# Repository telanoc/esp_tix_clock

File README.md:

=========================================================================

Module: esp tix clock

Date: 13 November 2015

Author: Pete Cervasio <cervasio@airmail.net>

=========================================================================

This project is a TIX clock running on an ESP-01 module.  Since the I/O
is limited, the two available pins are used for an i2c bus to drive a
port expander.  That handles the 27 LEDs as a 9x3 matrix using a ULN2803
and another transistor for the columns and three transistors to drive
the rows.  The other 4 pins read mostly-useless alarm setting buttons.
If only there was another output to use to drive some kind of alarmy
soundy thing.  Oops.  Perhaps I can modify the code so that it doesn't
send any serial data out, and take over the serial port pins.

So, what's a TIX clock?  Google is your friend, as are Bing and Yahoo.
And Youtube to an extent.

Features:

    ESP-01 module gets time from NTP - All you set is the access point
    & password.  You set the timezone before you compile.  Automatic
    changeover takes over from there.  Just don't move around a lot.
    :)

    Power is +5v, regulated to +3.3 for the ESP-01.  The clock in my
    living room is powered by your generic three-for-a-dollar USB
    power brick.

    Time library used to get NTP.  Modifications were made to make the
    time setting closer to msec accuracy (it's pretty close).  I got
    this from https://github.com/PaulStoffregen/Time if you want the
    original.

    WiFiManager used to auto-connect to the access point, and to set
    up the connection if necessary.  From AlexT
    (https://github.com/tzapu) but custom changes are stored in this
    repository.

    Timezone library (https://github.com/JChristensen/Timezone) used
    to handle automatic DST change.

    Display and Controller boards designed in Eagle 7.4 are included.
    The two boards are shared on Osh Park

        Display: https://www.oshpark.com/shared_projects/UMcsDmIr
     Controller: https://www.oshpark.com/shared_projects/IgKxO56E

    An alarm time can be set, but "oops, I need more pins"... there's
    no alarm output.  So it's not much of a feature after all.  As
	noted above, it should be possible to drop the serial port bits
	and take over those pins to be more gpio.

    A dumb 3d printed case will eventually be available on Tinkercad
    or Thingiverse or somewhere.  The one I have started is close but
    not quite there yet.

Caveats and whatnot:

    This was built using staging release esp8266-1.6.5-1160-gef26c5f

    Soldering SMTs by hand is a pain in the behind when you're older.

    Don't bring pin 9 of the display board to +5v without a current
    limiting resistor or you'll take out the 2n3904.  Don't ask how I
    know that...  the resistor on the control board should have been
    moved.
    
    ... ahh hindsight.

    male Power pins are long out the bottom of the control board to
    allow attaching a header for +5v.  That's how I did it.  If you
    have a better idea, please use it.  :)

Todo:

    Build a nice 3d printed case at the North Richland Hills Library
    Maker Spot.  I can't say enough good things about the most
    important building in NRH (and the highly important room upstairs
    that has all the fun makey bits in it).  If you live around Fort
    Worth, go visit.  It's a "soft" maker space, with no table saws or
    welder or whatnot, but that's what the Dallas maker space is good
    for.  :)

    Revamp the boards to bring out serial data, which would allow for
    setting more parameters and storing them in eeprom, like time zone
    values and stuff like that.

    Move that transistor base resistor to the display board.

Harware BOM:  This should be pretty accurate.

        1 - ESP-01
        1 - mcp23017 (so28w)
        1 - uln2803  (so18w)
        4 - MMBT3904 (sot23-bec)
        2 - BSS138 mosfets (sot-23)
        4 - standard through-hole tactile switches
        1 - AP2112K-3.3 regulator (sot-23-5)
        1 - 10uf 0805 capacitor
        2 - 0.1 uf 0805 capacitor
        1 - 1k 0805 resistor
        6 - 10k 0805 resistor
       27 - 68 ohm 0805 resistors
        3 - AA2214SURSK SMT blue LEDs
        6 - yellow SMT LEDs
        9 - red SMT LEDs
        9 - green SMT LEDs
        1 - 1x2 pin male header (extra long) 
        1 - 1x3 pin male header
        1 - 1x3 pin male header
        1 - 1x3 female header
        1 - 1x2 female header
        1 - 1x9 female header
        1 - 2x4 female header

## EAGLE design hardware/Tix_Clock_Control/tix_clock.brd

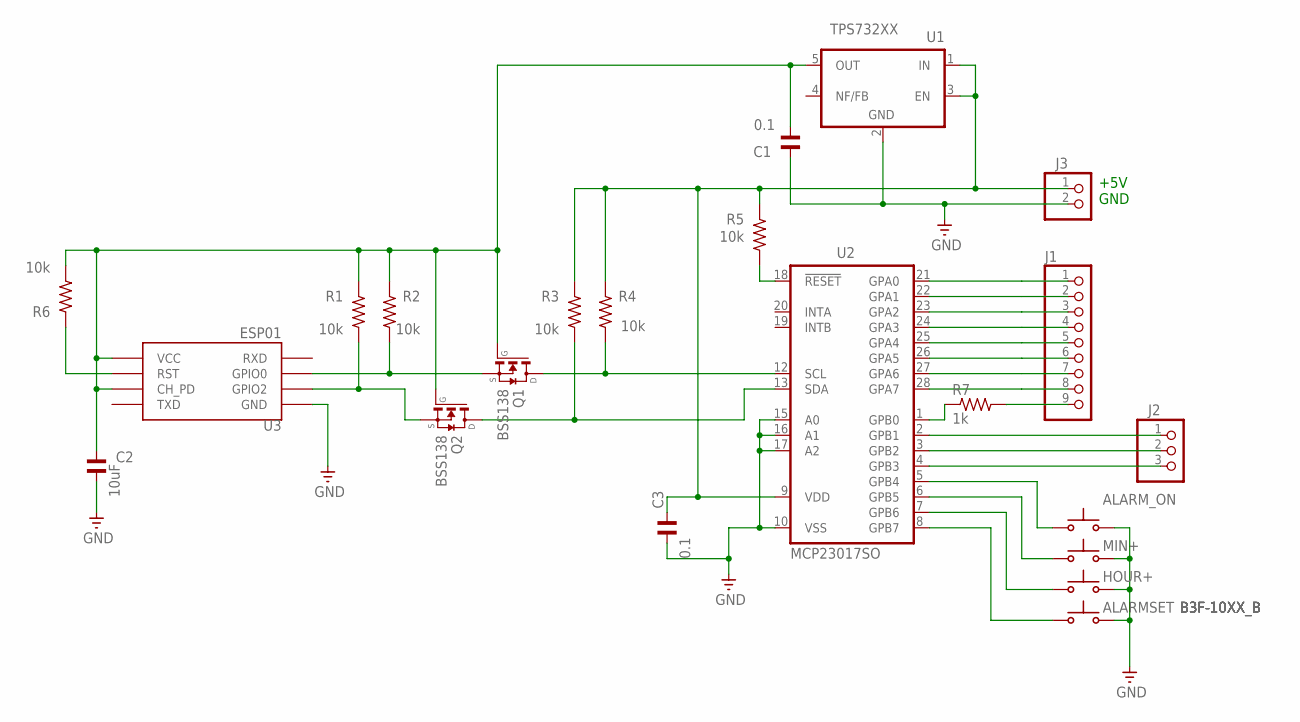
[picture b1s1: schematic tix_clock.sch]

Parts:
ALARMSET: B3F-10XX_B
ALARM_ON: B3F-10XX_B
C1, C3: 0.1; C0805
C2: 10uF; C0805
HOUR+: B3F-10XX_B
J1: PINHD-1X9; 1X09
J2: PINHD-1X3; 1X03
J3: PINHD-1X2; 1X02
MIN+: B3F-10XX_B
Q1, Q2: BSS138; SOT23
R1, R2, R3, R4, R5, R6: 10k; R0805
R7: 1k; R0805
U1: TPS732XX; SOT23-5
U2: MCP23017SO; SO28W
U3: ESP01

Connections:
GND: ALARMSET.3 (S), ALARMSET.4 (S), ALARM_ON.3 (S), ALARM_ON.4 (S), C1.2, C2.2, C3.2, HOUR+.3 (S), HOUR+.4 (S), J3.2, MIN+.3 (S), MIN+.4 (S), U1.2 (GND), U2.10 (VSS), U2.15 (A0), U2.16 (A1), U2.17 (A2), U3.GND
unnamed: J1.1, U2.21 (GPA0)
unnamed: J1.2, U2.22 (GPA1)
unnamed: J1.3, U2.23 (GPA2)
unnamed: J1.4, U2.24 (GPA3)
unnamed: J1.5, U2.25 (GPA4)
unnamed: J1.6, U2.26 (GPA5)
unnamed: J1.7, U2.27 (GPA6)
unnamed: J1.8, U2.28 (GPA7)
unnamed: J1.9, R7.2
unnamed: J2.1, U2.2 (GPB1)
unnamed: J2.2, U2.3 (GPB2)
unnamed: J2.3, U2.4 (GPB3)
unnamed: ALARM_ON.1, ALARM_ON.2, U2.5 (GPB4)
unnamed: MIN+.1, MIN+.2, U2.6 (GPB5)
unnamed: HOUR+.1, HOUR+.2, U2.7 (GPB6)
unnamed: ALARMSET.1, ALARMSET.2, U2.8 (GPB7)
unnamed: R7.1, U2.1 (GPB0)
unnamed: Q1.3 (D), R4.1, U2.12 (SCL)
unnamed: Q2.3 (D), R3.1, U2.13 (SDA)
unnamed: Q1.2 (S), R2.1, U3.GPIO0
unnamed: Q2.2 (S), R1.1, U3.GPIO2
unnamed: R5.1, U2.18 (!RESET)
unnamed: R6.1, U3.RST
VCC: C1.1, C2.1, Q1.1 (G), Q2.1 (G), R1.2, R2.2, R6.2, U1.5 (OUT), U3.CH_PD, U3.VCC
VDD: C3.1, J3.1, R3.2, R4.2, R5.2, U1.1 (IN), U1.3 (EN), U2.9 (VDD)

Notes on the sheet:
+5V GND

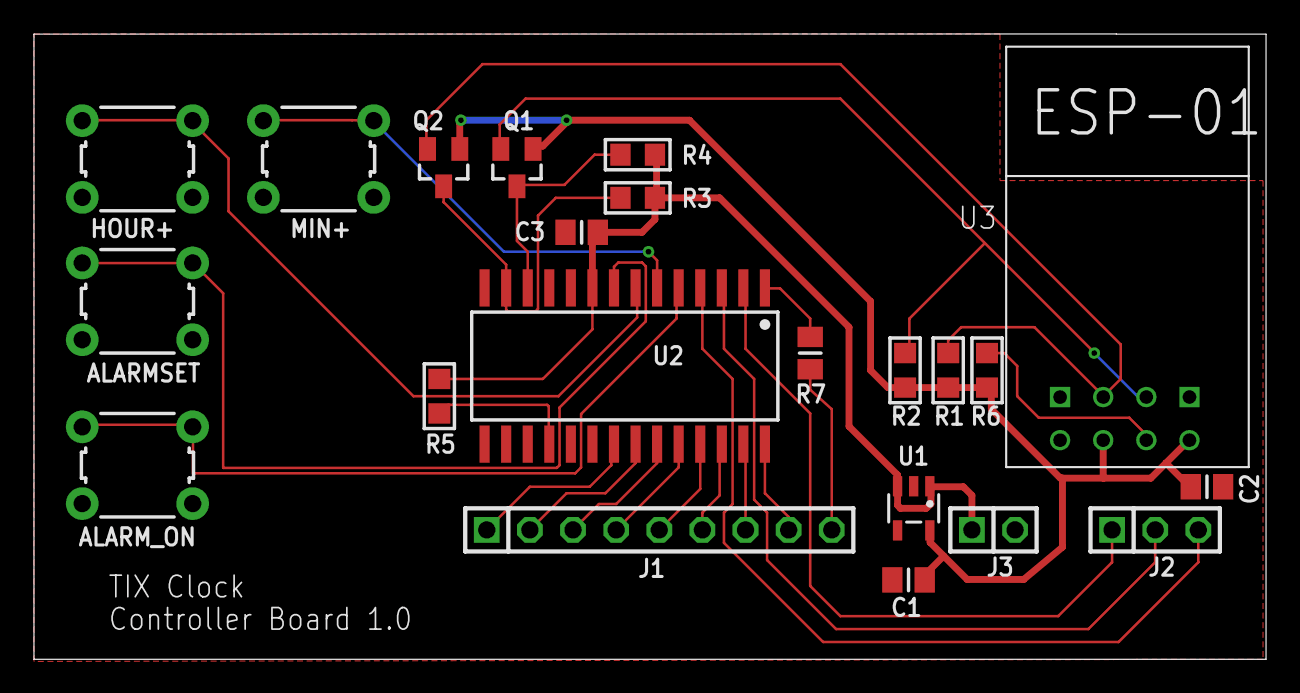
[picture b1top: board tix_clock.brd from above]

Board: 2 copper layers, 72.6 x 36.8 mm, 22 parts (0 on the bottom side), 26 nets.

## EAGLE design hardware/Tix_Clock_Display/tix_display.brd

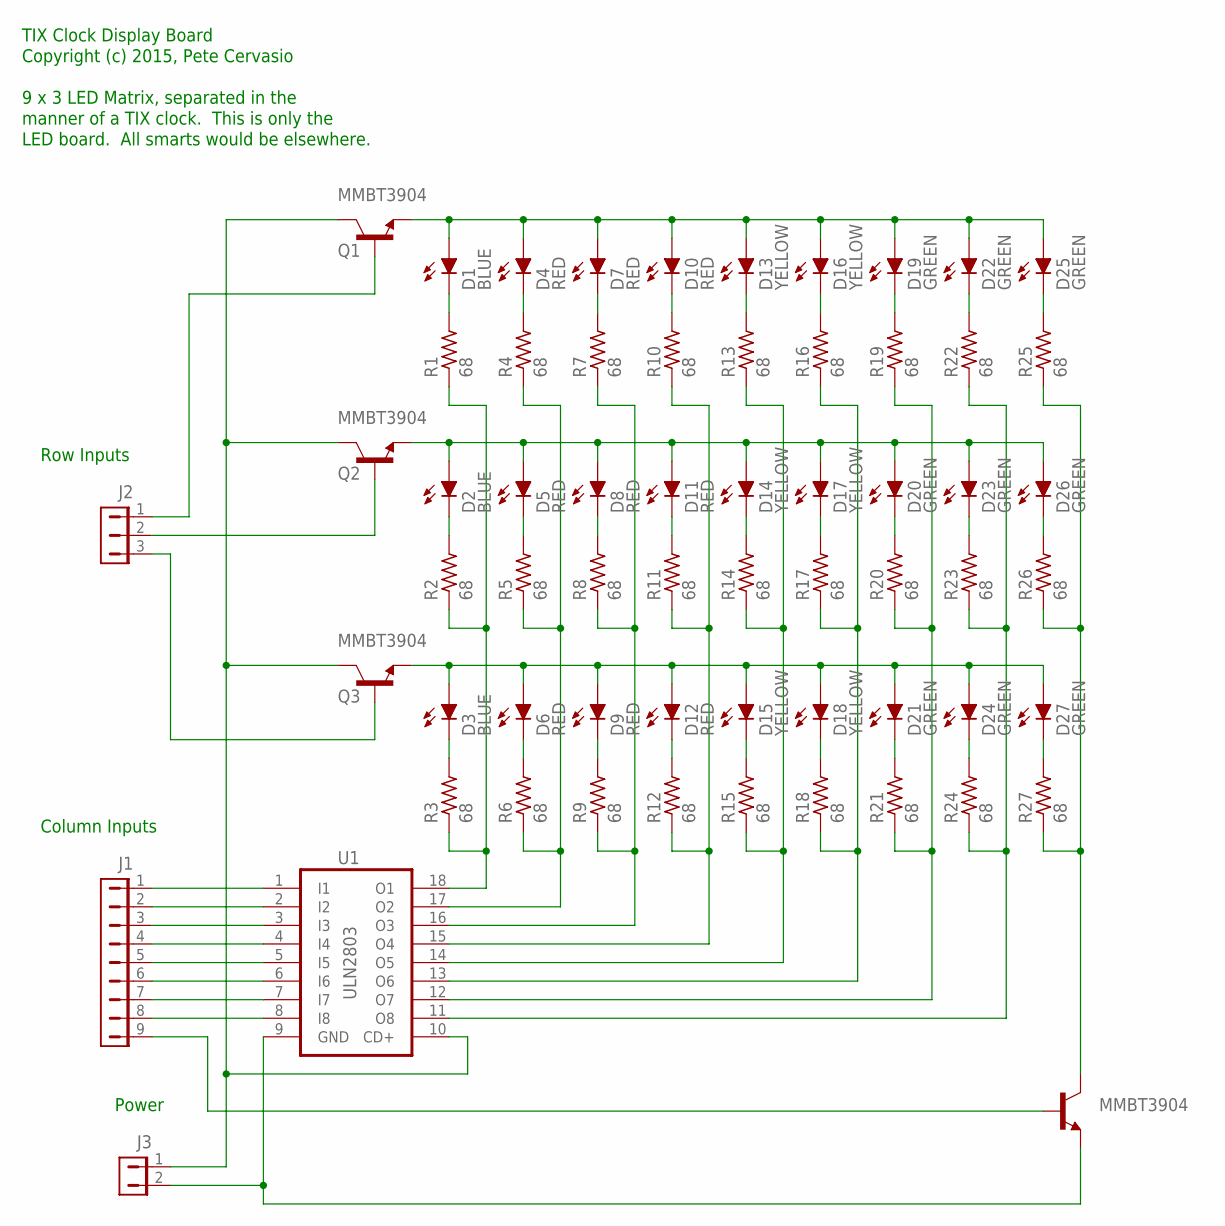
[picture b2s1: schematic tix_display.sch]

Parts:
D1, D2, D3: BLUE; AA2214SURSK
D4, D5, D6, D7, D8, D9, D10, D11, D12: RED; AA2214SURSK
D13, D14, D15, D16, D17, D18: YELLOW; AA2214SURSK
D19, D20, D21, D22, D23, D24, D25, D26, D27: GREEN; AA2214SURSK
J1: MTA09-100
J2: MTA03-100
J3: MTA02-100
Q1, Q2, Q3, Q4: MMBT3904; SOT23-BEC
R1, R2, R3, R4, R5, R6, R7, R8, R9, R10, R11, R12, R13, R14, R15, R16, R17, R18, R19, R20, R21, R22, R23, R24, R25, R26, R27: 68; M0805
U1: ULN2803; SO18W

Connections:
GND: J3.2, Q4.E, U1.9 (GND)
LEDCOL1: R1.1, R2.1, R3.1, U1.18 (O1)
LEDCOL2: R4.1, R5.1, R6.1, U1.17 (O2)
LEDCOL3: R7.1, R8.1, R9.1, U1.16 (O3)
LEDCOL4: R10.1, R11.1, R12.1, U1.15 (O4)
LEDCOL5: R13.1, R14.1, R15.1, U1.14 (O5)
LEDCOL6: R16.1, R17.1, R18.1, U1.13 (O6)
LEDCOL7: R19.1, R20.1, R21.1, U1.12 (O7)
LEDCOL8: R22.1, R23.1, R24.1, U1.11 (O8)
LEDCOL9: Q4.C, R25.1, R26.1, R27.1
unnamed: D1.A, D4.A, D7.A, D10.A, D13.A, D16.A, D19.A, D22.A, D25.A, Q1.E
unnamed: D2.A, D5.A, D8.A, D11.A, D14.A, D17.A, D20.A, D23.A, D26.A, Q2.E
unnamed: D3.A, D6.A, D9.A, D12.A, D15.A, D18.A, D21.A, D24.A, D27.A, Q3.E
unnamed: D3.C, R3.2
unnamed: D27.C, R27.2
unnamed: J2.1, Q1.B
unnamed: D24.C, R24.2
unnamed: J2.2, Q2.B
unnamed: D21.C, R21.2
unnamed: D18.C, R18.2
unnamed: D15.C, R15.2
unnamed: D12.C, R12.2
unnamed: D9.C, R9.2
unnamed: D6.C, R6.2
unnamed: D2.C, R2.2
unnamed: D5.C, R5.2
unnamed: D8.C, R8.2
unnamed: D11.C, R11.2
unnamed: D14.C, R14.2
unnamed: D17.C, R17.2
unnamed: D20.C, R20.2
unnamed: D23.C, R23.2
unnamed: D26.C, R26.2
unnamed: D1.C, R1.2
unnamed: D25.C, R25.2
unnamed: D22.C, R22.2
unnamed: D19.C, R19.2
unnamed: D16.C, R16.2
unnamed: D13.C, R13.2
unnamed: D10.C, R10.2
unnamed: D7.C, R7.2
unnamed: D4.C, R4.2
unnamed: J2.3, Q3.B
unnamed: J1.1, U1.1 (I1)
unnamed: J1.2, U1.2 (I2)
unnamed: J1.3, U1.3 (I3)
unnamed: J1.4, U1.4 (I4)
unnamed: J1.5, U1.5 (I5)
unnamed: J1.6, U1.6 (I6)
unnamed: J1.7, U1.7 (I7)
unnamed: J1.8, U1.8 (I8)
unnamed: J1.9, Q4.B
VCC: J3.1, Q1.C, Q2.C, Q3.C, U1.10 (CD+)

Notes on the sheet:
Row Inputs
Column Inputs
Power
TIX Clock Display Board Copyright (c) 2015, Pete Cervasio 9 x 3 LED Matrix, separated in the manner of a TIX clock. This is only the LED board. All smarts would be elsewhere.

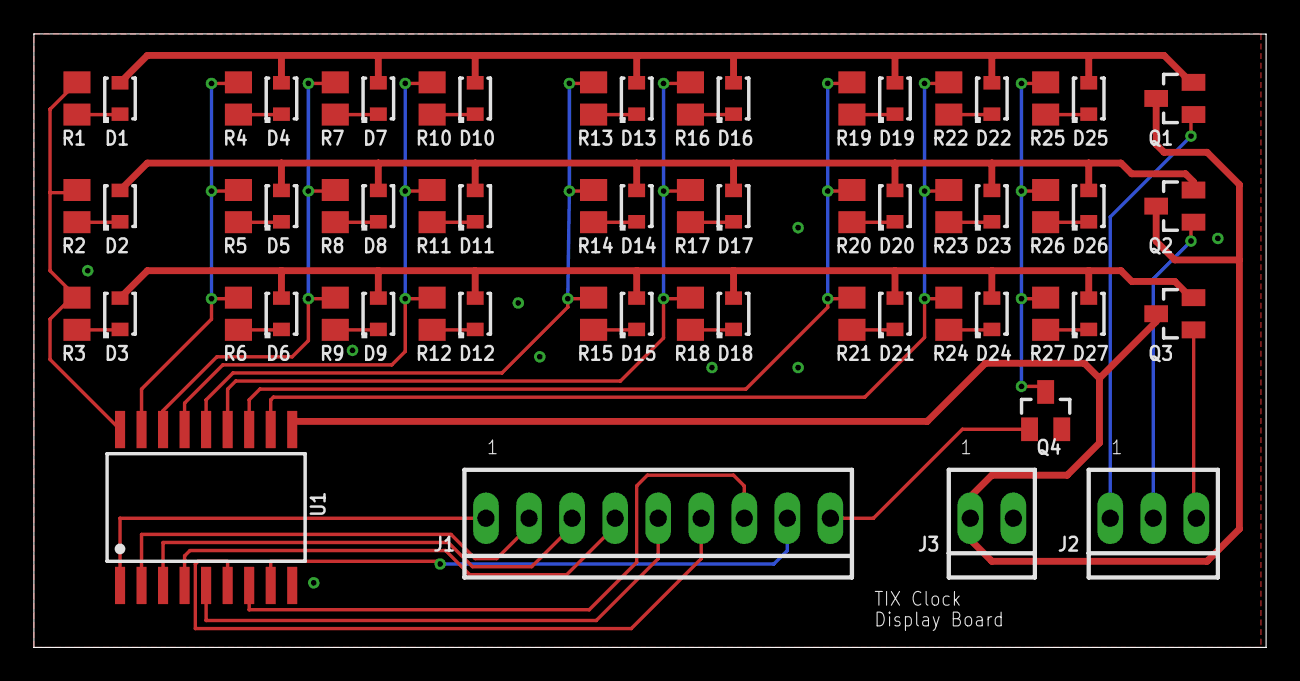
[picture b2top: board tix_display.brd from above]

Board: 2 copper layers, 72.7 x 36.2 mm, 62 parts (0 on the bottom side), 53 nets.

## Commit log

2015-11-14 Initial import of project files
2015-11-14 add url for osh park boards
2015-11-14 formatting
2015-12-09 Documentation changes

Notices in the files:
parts and their libraries:
rc-master-smd: Copyright (C) 2007-2008, Bob Starr
